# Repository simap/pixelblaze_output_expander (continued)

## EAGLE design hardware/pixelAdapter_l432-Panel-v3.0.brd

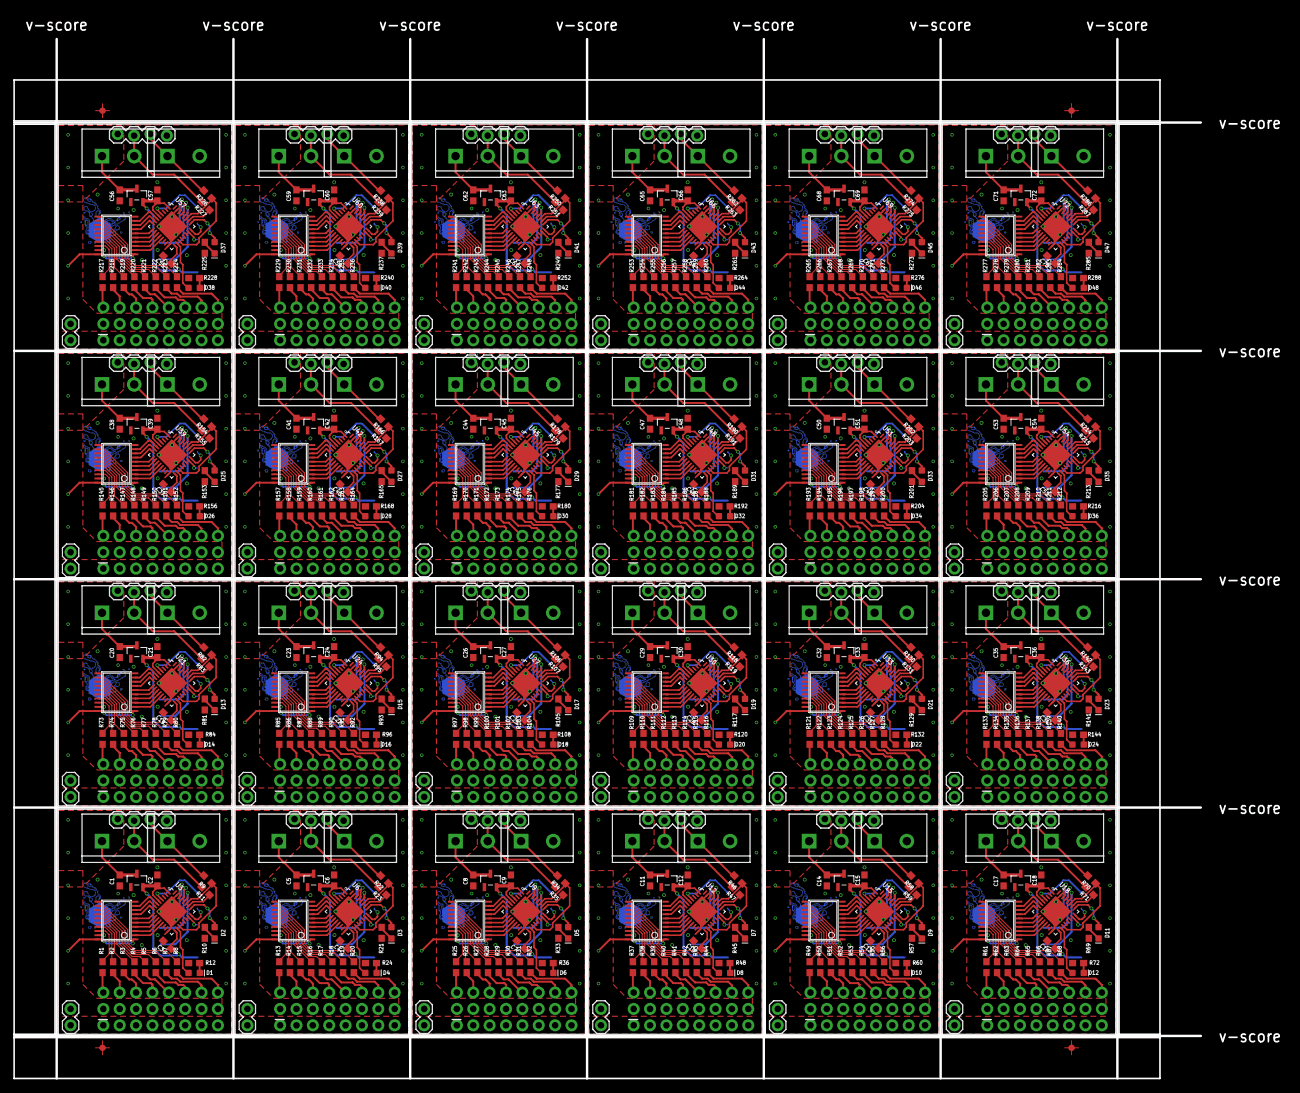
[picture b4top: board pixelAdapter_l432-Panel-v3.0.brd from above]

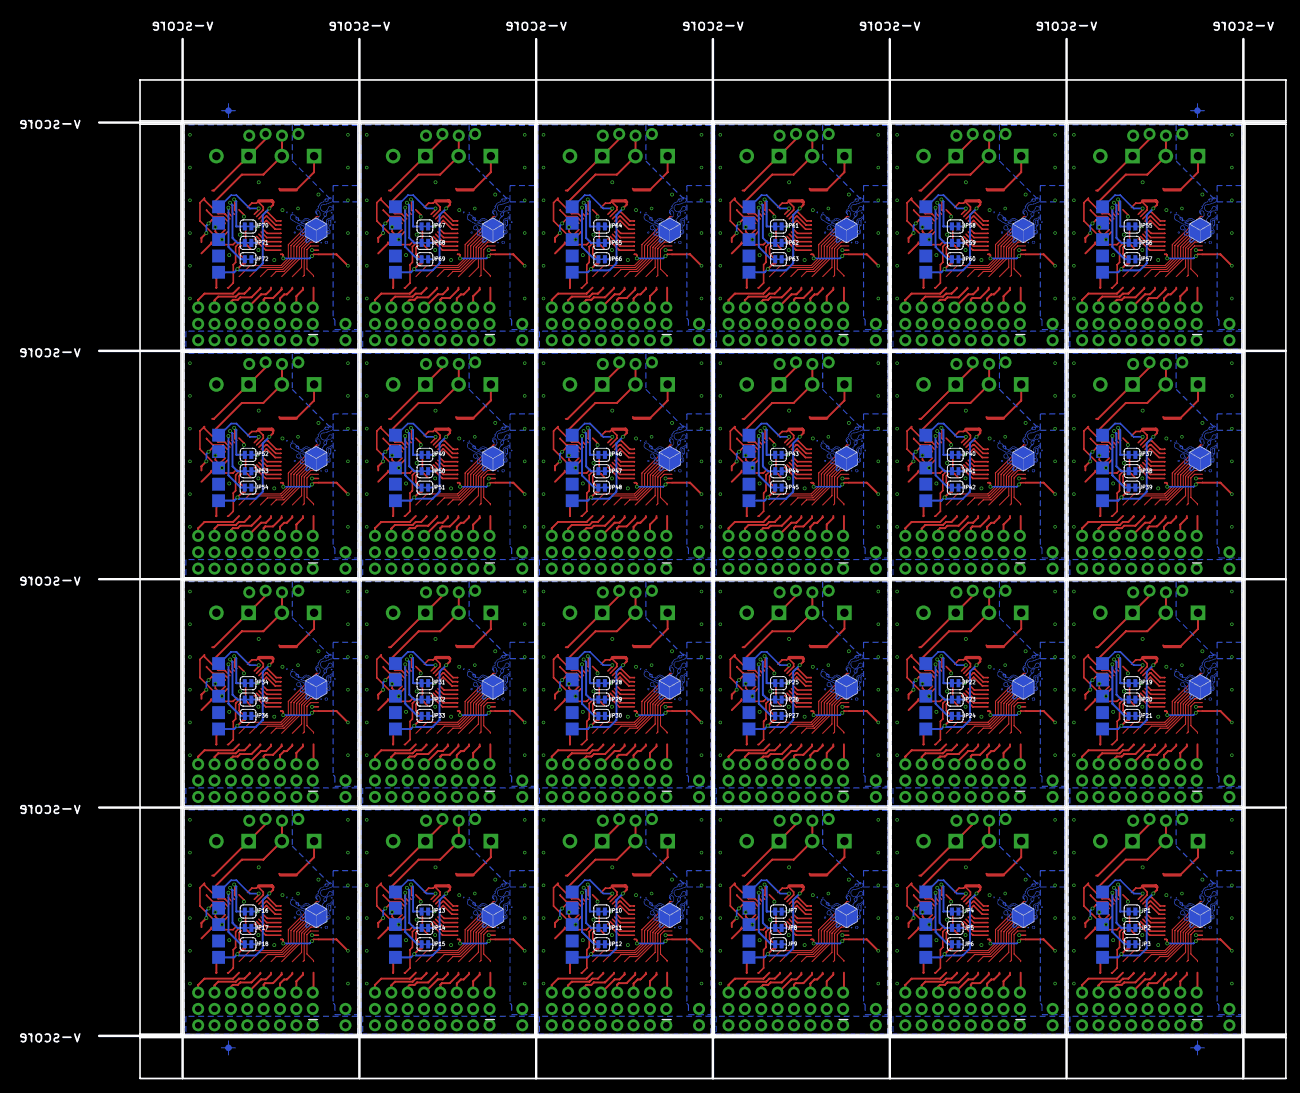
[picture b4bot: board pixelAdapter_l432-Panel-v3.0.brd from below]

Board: 2 copper layers, 184.2 x 161.3 mm, 848 parts (220 on the bottom side), 984 nets.

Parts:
C1, C2, C5, C6, C8, C9, C11, C12, C14, C15, C17, C18, C20, C21, C23, C24, C26, C27, C29, C30, C32, C33, C35, C36, C38, C39, C41, C42, C44, C45, C47, C48, C50, C51, C53, C54, C56, C57, C59, C60, C62, C63, C65, C66, C68, C69, C71, C72: 4.7uF; 0603
C3, C4, C7, C10, C13, C16, C19, C22, C25, C28, C31, C34, C37, C40, C43, C46, C49, C52, C55, C58, C61, C64, C67, C70: 0.1uF; 0603
D1, D4, D6, D8, D10, D12, D14, D16, D18, D20, D22, D24, D26, D28, D30, D32, D34, D36, D38, D40, D42, D44, D46, D48: GREEN; LED-0603
D2, D3, D5, D7, D9, D11, D13, D15, D17, D19, D21, D23, D25, D27, D29, D31, D33, D35, D37, D39, D41, D43, D45, D47: ORANGE; LED-0603
E$1, E$2, E$3, E$4, E$5, E$6, E$7, E$8: BENSFIDUCIAL-SMALL
J1, J11, J17, J23, J29, J35, J41, J47, J53, J59, J65, J71, J77, J83, J89, J95, J101, J107, J113, J119, J125, J131, J137, J143: 1X08_NO_SILK
J2, J7, J13, J19, J25, J31, J37, J43, J49, J55, J61, J67, J73, J79, J85, J91, J97, J103, J109, J115, J121, J127, J133, J139: 2X8-NOSILK
J3, J4, J8, J9, J14, J15, J20, J21, J26, J27, J32, J33, J38, J39, J44, J45, J50, J51, J56, J57, J62, J63, J68, J69, J74, J75, J80, J81, J86, J87, J92, J93, J98, J99, J104, J105, J110, J111, J116, J117, J122, J123, J128, J129, J134, J135, J140, J141: SCREWTERMINAL-5MM-2
J5, J10, J16, J22, J28, J34, J40, J46, J52, J58, J64, J70, J76, J82, J88, J94, J100, J106, J112, J118, J124, J130, J136, J142: 1X04_LOCK
J6, J12, J18, J24, J30, J36, J42, J48, J54, J60, J66, J72, J78, J84, J90, J96, J102, J108, J114, J120, J126, J132, J138, J144: 1X02
JP1, JP2, JP3, JP4, JP5, JP6, JP7, JP8, JP9, JP10, JP11, JP12, JP13, JP14, JP15, JP16, JP17, JP18, JP19, JP20, JP21, JP22, JP23, JP24, JP25, JP26, JP27, JP28, JP29, JP30, JP31, JP32, JP33, JP34, JP35, JP36, JP37, JP38, JP39, JP40, JP41, JP42, JP43, JP44, JP45, JP46, JP47, JP48, JP49, JP50, JP51, JP52, JP53, JP54, JP55, JP56, JP57, JP58, JP59, JP60, JP61, JP62, JP63, JP64, JP65, JP66, JP67, JP68, JP69, JP70, JP71, JP72: JUMPER-SMT_2_NC_TRACE_SILK; SMT-JUMPER_2_NC_TRACE_SILK
R1, R2, R3, R4, R5, R6, R7, R8, R9, R10, R11, R12, R13, R14, R15, R16, R17, R18, R19, R20, R21, R22, R23, R24, R25, R26, R27, R28, R29, R30, R31, R32, R33, R34, R35, R36, R37, R38, R39, R40, R41, R42, R43, R44, R45, R46, R47, R48, R49, R50, R51, R52, R53, R54, R55, R56, R57, R58, R59, R60, R61, R62, R63, R64, R65, R66, R67, R68, R69, R70, R71, R72, R73, R74, R75, R76, R77, R78, R79, R80, R81, R82, R83, R84, R85, R86, R87, R88, R89, R90, R91, R92, R93, R94, R95, R96, R97, R98, R99, R100, R101, R102, R103, R104, R105, R106, R107, R108, R109, R110, R111, R112, R113, R114, R115, R116, R117, R118, R119, R120, R121, R122, R123, R124, R125, R126, R127, R128, R129, R130, R131, R132, R133, R134, R135, R136, R137, R138, R139, R140, R141, R142, R143, R144, R145, R146, R147, R148, R149, R150, R151, R152, R153, R154, R155, R156, R157, R158, R159, R160, R161, R162, R163, R164, R165, R166, R167, R168, R169, R170, R171, R172, R173, R174, R175, R176, R177, R178, R179, R180, R181, R182, R183, R184, R185, R186, R187, R188, R189, R190, R191, R192, R193, R194, R195, R196, R197, R198, R199, R200, R201, R202, R203, R204, R205, R206, R207, R208, R209, R210, R211, R212, R213, R214, R215, R216, R217, R218, R219, R220, R221, R222, R223, R224, R225, R226, R227, R228, R229, R230, R231, R232, R233, R234, R235, R236, R237, R238, R239, R240, R241, R242, R243, R244, R245, R246, R247, R248, R249, R250, R251, R252, R253, R254, R255, R256, R257, R258, R259, R260, R261, R262, R263, R264, R265, R266, R267, R268, R269, R270, R271, R272, R273, R274, R275, R276, R277, R278, R279, R280, R281, R282, R283, R284, R285, R286, R287, R288: 100; 0603
TP1, TP2, TP3, TP4, TP5, TP6, TP7, TP8, TP9, TP10, TP11, TP12, TP13, TP14, TP15, TP16, TP17, TP18, TP19, TP20, TP21, TP22, TP23, TP24, TP25, TP26, TP27, TP28, TP29, TP30, TP31, TP32, TP33, TP34, TP35, TP36, TP37, TP38, TP39, TP40, TP41, TP42, TP43, TP44, TP45, TP46, TP47, TP48, TP49, TP50, TP51, TP52, TP53, TP54, TP55, TP56, TP57, TP58, TP59, TP60, TP61, TP62, TP63, TP64, TP65, TP66, TP67, TP68, TP69, TP70, TP71, TP72, TP73, TP74, TP75, TP76, TP77, TP78, TP79, TP80, TP81, TP82, TP83, TP84, TP85, TP86, TP87, TP88, TP89, TP90, TP91, TP92, TP93, TP94, TP95, TP96, TP97, TP98, TP99, TP100, TP101, TP102, TP103, TP104, TP105, TP106, TP107, TP108, TP109, TP110, TP111, TP112, TP113, TP114, TP115, TP116, TP117, TP118, TP119, TP120: TPTP20SQ; TP20SQ
U1, U4, U7, U10, U13, U16, U19, U22, U25, U28, U31, U34, U37, U40, U43, U46, U49, U52, U55, U58, U61, U64, U67, U70: SN74HCT245PWR; TSSOP20
U2, U5, U8, U11, U14, U17, U20, U23, U26, U29, U32, U35, U38, U41, U44, U47, U50, U53, U56, U59, U62, U65, U68, U71: AP2120N-3.3TRG1; SOT95P237X112-3N
U3, U6, U9, U12, U15, U18, U21, U24, U27, U30, U33, U36, U39, U42, U45, U48, U51, U54, U57, U60, U63, U66, U69, U72: STM32L432KCU6; QFN50P500X500X60-33N
U$1, U$2, U$3, U$4, U$5, U$6, U$7, U$8, U$9, U$10, U$11, U$12, U$13, U$14, U$15, U$16, U$17, U$18, U$19, U$20, U$21, U$22, U$23, U$24: ELECTRO_MAGE_PCB4_PIXEL_2#PNG

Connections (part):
5V: C1.1, J2.1, J2.3, J2.5, J2.7, J2.9, J2.11, J2.13, J2.15, J3.1, J5.4, J6.2, U1.1, U1.20, U2.3
5V1: C5.1, J7.1, J7.3, J7.5, J7.7, J7.9, J7.11, J7.13, J7.15, J8.1, J10.4, J12.2, U4.1, U4.20, U5.3
5V2: C8.1, J13.1, J13.3, J13.5, J13.7, J13.9, J13.11, J13.13, J13.15, J14.1, J16.4, J18.2, U7.1, U7.20, U8.3
5V3: C11.1, J19.1, J19.3, J19.5, J19.7, J19.9, J19.11, J19.13, J19.15, J20.1, J22.4, J24.2, U10.1, U10.20, U11.3
5V4: C14.1, J25.1, J25.3, J25.5, J25.7, J25.9, J25.11, J25.13, J25.15, J26.1, J28.4, J30.2, U13.1, U13.20, U14.3
5V5: C17.1, J31.1, J31.3, J31.5, J31.7, J31.9, J31.11, J31.13, J31.15, J32.1, J34.4, J36.2, U16.1, U16.20, U17.3
5V6: C20.1, J37.1, J37.3, J37.5, J37.7, J37.9, J37.11, J37.13, J37.15, J38.1, J40.4, J42.2, U19.1, U19.20, U20.3
5V7: C23.1, J43.1, J43.3, J43.5, J43.7, J43.9, J43.11, J43.13, J43.15, J44.1, J46.4, J48.2, U22.1, U22.20, U23.3
5V8: C26.1, J49.1, J49.3, J49.5, J49.7, J49.9, J49.11, J49.13, J49.15, J50.1, J52.4, J54.2, U25.1, U25.20, U26.3
5V9: C29.1, J55.1, J55.3, J55.5, J55.7, J55.9, J55.11, J55.13, J55.15, J56.1, J58.4, J60.2, U28.1, U28.20, U29.3
5V10: C32.1, J61.1, J61.3, J61.5, J61.7, J61.9, J61.11, J61.13, J61.15, J62.1, J64.4, J66.2, U31.1, U31.20, U32.3
5V11: C35.1, J67.1, J67.3, J67.5, J67.7, J67.9, J67.11, J67.13, J67.15, J68.1, J70.4, J72.2, U34.1, U34.20, U35.3
5V12: C38.1, J73.1, J73.3, J73.5, J73.7, J73.9, J73.11, J73.13, J73.15, J74.1, J76.4, J78.2, U37.1, U37.20, U38.3
5V13: C41.1, J79.1, J79.3, J79.5, J79.7, J79.9, J79.11, J79.13, J79.15, J80.1, J82.4, J84.2, U40.1, U40.20, U41.3
5V14: C44.1, J85.1, J85.3, J85.5, J85.7, J85.9, J85.11, J85.13, J85.15, J86.1, J88.4, J90.2, U43.1, U43.20, U44.3
5V15: C47.1, J91.1, J91.3, J91.5, J91.7, J91.9, J91.11, J91.13, J91.15, J92.1, J94.4, J96.2, U46.1, U46.20, U47.3
5V16: C50.1, J97.1, J97.3, J97.5, J97.7, J97.9, J97.11, J97.13, J97.15, J98.1, J100.4, J102.2, U49.1, U49.20, U50.3
5V17: C53.1, J103.1, J103.3, J103.5, J103.7, J103.9, J103.11, J103.13, J103.15, J104.1, J106.4, J108.2, U52.1, U52.20, U53.3
5V18: C56.1, J109.1, J109.3, J109.5, J109.7, J109.9, J109.11, J109.13, J109.15, J110.1, J112.4, J114.2, U55.1, U55.20, U56.3
5V19: C59.1, J115.1, J115.3, J115.5, J115.7, J115.9, J115.11, J115.13, J115.15, J116.1, J118.4, J120.2, U58.1, U58.20, U59.3
5V20: C62.1, J121.1, J121.3, J121.5, J121.7, J121.9, J121.11, J121.13, J121.15, J122.1, J124.4, J126.2, U61.1, U61.20, U62.3
5V21: C65.1, J127.1, J127.3, J127.5, J127.7, J127.9, J127.11, J127.13, J127.15, J128.1, J130.4, J132.2, U64.1, U64.20, U65.3
5V22: C68.1, J133.1, J133.3, J133.5, J133.7, J133.9, J133.11, J133.13, J133.15, J134.1, J136.4, J138.2, U67.1, U67.20, U68.3
5V23: C71.1, J139.1, J139.3, J139.5, J139.7, J139.9, J139.11, J139.13, J139.15, J140.1, J142.4, J144.2, U70.1, U70.20, U71.3
+3V1: C4.1, C6.1, TP9.TP, U5.2, U6.1, U6.5, U6.17
+3V2: C7.1, C9.1, TP14.TP, U8.2, U9.1, U9.5, U9.17
+3V3: C2.1, C3.1, TP4.TP, U2.2, U3.1, U3.5, U3.17
+3V4: C10.1, C12.1, TP19.TP, U11.2, U12.1, U12.5, U12.17
+3V5: C13.1, C15.1, TP24.TP, U14.2, U15.1, U15.5, U15.17
+3V6: C16.1, C18.1, TP29.TP, U17.2, U18.1, U18.5, U18.17
+3V7: C19.1, C21.1, TP34.TP, U20.2, U21.1, U21.5, U21.17
+3V8: C22.1, C24.1, TP39.TP, U23.2, U24.1, U24.5, U24.17
+3V9: C25.1, C27.1, TP44.TP, U26.2, U27.1, U27.5, U27.17
+3V10: C28.1, C30.1, TP49.TP, U29.2, U30.1, U30.5, U30.17
+3V11: C31.1, C33.1, TP54.TP, U32.2, U33.1, U33.5, U33.17
+3V12: C34.1, C36.1, TP59.TP, U35.2, U36.1, U36.5, U36.17
+3V13: C37.1, C39.1, TP64.TP, U38.2, U39.1, U39.5, U39.17
+3V14: C40.1, C42.1, TP69.TP, U41.2, U42.1, U42.5, U42.17
+3V15: C43.1, C45.1, TP74.TP, U44.2, U45.1, U45.5, U45.17
+3V16: C46.1, C48.1, TP79.TP, U47.2, U48.1, U48.5, U48.17
+3V17: C49.1, C51.1, TP84.TP, U50.2, U51.1, U51.5, U51.17
+3V18: C52.1, C54.1, TP89.TP, U53.2, U54.1, U54.5, U54.17
+3V19: C55.1, C57.1, TP94.TP, U56.2, U57.1, U57.5, U57.17
+3V20: C58.1, C60.1, TP99.TP, U59.2, U60.1, U60.5, U60.17
+3V21: C61.1, C63.1, TP104.TP, U62.2, U63.1, U63.5, U63.17
+3V22: C64.1, C66.1, TP109.TP, U65.2, U66.1, U66.5, U66.17
+3V23: C67.1, C69.1, TP114.TP, U68.2, U69.1, U69.5, U69.17
+3V24: C70.1, C72.1, TP119.TP, U71.2, U72.1, U72.5, U72.17
CH0: U1.2, U3.13
CH1: U1.3, U3.12
CH2: U1.4, U3.11
CH3: U1.5, U3.10
CH4: U1.6, U3.9
CH5: U1.7, U3.8
CH6: U1.8, U3.7
CH7: U1.9, U3.6
CH8: U4.9, U6.6
CH9: U4.8, U6.7
CH10: U4.7, U6.8
CH11: U4.2, U6.13
CH12: U4.3, U6.12
CH13: U4.4, U6.11
CH14: U4.5, U6.10
CH15: U4.6, U6.9
CH16: U7.9, U9.6
CH17: U7.8, U9.7
CH18: U7.7, U9.8
CH19: U7.2, U9.13
CH20: U7.3, U9.12
CH21: U7.4, U9.11
CH22: U7.5, U9.10
CH23: U7.6, U9.9
CH24: U10.9, U12.6
CH25: U10.8, U12.7
CH26: U10.7, U12.8
CH27: U10.2, U12.13
CH28: U10.3, U12.12
CH29: U10.4, U12.11
CH30: U10.5, U12.10
CH31: U10.6, U12.9
CH32: U13.9, U15.6
CH33: U13.8, U15.7
CH34: U13.7, U15.8
CH35: U13.2, U15.13
CH36: U13.3, U15.12
CH37: U13.4, U15.11
CH38: U13.5, U15.10
CH39: U13.6, U15.9
CH40: U16.9, U18.6
CH41: U16.8, U18.7
CH42: U16.7, U18.8
CH43: U16.2, U18.13
CH44: U16.3, U18.12
CH45: U16.4, U18.11
CH46: U16.5, U18.10
CH47: U16.6, U18.9
CH48: U19.9, U21.6
CH49: U19.8, U21.7
CH50: U19.7, U21.8
CH51: U19.2, U21.13
CH52: U19.3, U21.12
CH53: U19.4, U21.11
CH54: U19.5, U21.10
CH55: U19.6, U21.9
CH56: U22.9, U24.6
CH57: U22.8, U24.7
CH58: U22.7, U24.8
CH59: U22.2, U24.13
CH60: U22.3, U24.12
CH61: U22.4, U24.11
CH62: U22.5, U24.10
CH63: U22.6, U24.9
CH64: U25.9, U27.6
CH65: U25.8, U27.7
CH66: U25.7, U27.8
CH67: U25.2, U27.13
CH68: U25.3, U27.12
CH69: U25.4, U27.11
CH70: U25.5, U27.10
CH71: U25.6, U27.9
CH72: U28.9, U30.6
CH73: U28.8, U30.7
CH74: U28.7, U30.8
CH75: U28.2, U30.13
CH76: U28.3, U30.12
CH77: U28.4, U30.11
CH78: U28.5, U30.10
CH79: U28.6, U30.9
CH80: U31.9, U33.6
CH81: U31.8, U33.7
CH82: U31.7, U33.8
CH83: U31.2, U33.13
CH84: U31.3, U33.12
CH85: U31.4, U33.11
CH86: U31.5, U33.10
CH87: U31.6, U33.9
CH88: U34.9, U36.6
CH89: U34.8, U36.7
CH90: U34.7, U36.8
CH91: U34.2, U36.13
CH92: U34.3, U36.12
CH93: U34.4, U36.11
CH94: U34.5, U36.10
CH95: U34.6, U36.9
CH96: U37.9, U39.6
CH97: U37.8, U39.7
CH98: U37.7, U39.8
CH99: U37.2, U39.13
CH100: U37.3, U39.12
CH101: U37.4, U39.11
CH102: U37.5, U39.10
CH103: U37.6, U39.9
CH104: U40.9, U42.6
CH105: U40.8, U42.7
CH106: U40.7, U42.8
CH107: U40.2, U42.13
CH108: U40.3, U42.12
CH109: U40.4, U42.11
CH110: U40.5, U42.10
CH111: U40.6, U42.9
CH112: U43.9, U45.6
CH113: U43.8, U45.7
CH114: U43.7, U45.8
CH115: U43.2, U45.13
CH116: U43.3, U45.12
CH117: U43.4, U45.11
CH118: U43.5, U45.10
CH119: U43.6, U45.9
CH120: U46.9, U48.6
CH121: U46.8, U48.7
CH122: U46.7, U48.8
CH123: U46.2, U48.13
CH124: U46.3, U48.12
CH125: U46.4, U48.11
CH126: U46.5, U48.10
CH127: U46.6, U48.9
CH128: U49.9, U51.6
CH129: U49.8, U51.7
CH130: U49.7, U51.8
CH131: U49.2, U51.13
CH132: U49.3, U51.12
CH133: U49.4, U51.11
CH134: U49.5, U51.10
CH135: U49.6, U51.9
CH136: U52.9, U54.6
CH137: U52.8, U54.7
CH138: U52.7, U54.8
CH139: U52.2, U54.13
CH140: U52.3, U54.12
CH141: U52.4, U54.11
CH142: U52.5, U54.10
CH143: U52.6, U54.9
CH144: U55.9, U57.6
CH145: U55.8, U57.7
CH146: U55.7, U57.8
CH147: U55.2, U57.13
CH148: U55.3, U57.12
CH149: U55.4, U57.11
CH150: U55.5, U57.10
CH151: U55.6, U57.9
CH152: U58.9, U60.6
CH153: U58.8, U60.7
CH154: U58.7, U60.8
CH155: U58.2, U60.13
CH156: U58.3, U60.12
CH157: U58.4, U60.11
CH158: U58.5, U60.10
CH159: U58.6, U60.9
CH160: U61.9, U63.6
CH161: U61.8, U63.7
CH162: U61.7, U63.8
CH163: U61.2, U63.13
CH164: U61.3, U63.12
CH165: U61.4, U63.11
CH166: U61.5, U63.10
CH167: U61.6, U63.9
CH168: U64.9, U66.6
CH169: U64.8, U66.7
CH170: U64.7, U66.8
CH171: U64.2, U66.13
CH172: U64.3, U66.12
CH173: U64.4, U66.11
CH174: U64.5, U66.10
CH175: U64.6, U66.9
CH176: U67.9, U69.6
CH177: U67.8, U69.7
CH178: U67.7, U69.8
CH179: U67.2, U69.13
CH180: U67.3, U69.12
CH181: U67.4, U69.11
CH182: U67.5, U69.10
CH183: U67.6, U69.9
CH184: U70.9, U72.6
CH185: U70.8, U72.7
CH186: U70.7, U72.8
CH187: U70.2, U72.13
CH188: U70.3, U72.12
CH189: U70.4, U72.11
CH190: U70.5, U72.10
CH191: U70.6, U72.9
CLK: R11.1, U3.26
CLK1: R23.1, U6.26
CLK2: R35.1, U9.26
CLK3: R47.1, U12.26
CLK4: R59.1, U15.26
CLK5: R71.1, U18.26
CLK6: R83.1, U21.26
CLK7: R95.1, U24.26
CLK8: R107.1, U27.26
CLK9: R119.1, U30.26
CLK10: R131.1, U33.26
CLK11: R143.1, U36.26
CLK12: R155.1, U39.26
CLK13: R167.1, U42.26
CLK14: R179.1, U45.26
CLK15: R191.1, U48.26
CLK16: R203.1, U51.26
CLK17: R215.1, U54.26
CLK18: R227.1, U57.26
CLK19: R239.1, U60.26
CLK20: R251.1, U63.26
CLK21: R263.1, U66.26
CLK22: R275.1, U69.26
CLK23: R287.1, U72.26
CLK_IN: J3.2, J5.3, R11.2
CLK_IN1: J8.2, J10.3, R23.2
CLK_IN2: J14.2, J16.3, R35.2
CLK_IN3: J20.2, J22.3, R47.2
CLK_IN4: J26.2, J28.3, R59.2
CLK_IN5: J32.2, J34.3, R71.2
CLK_IN6: J38.2, J40.3, R83.2
CLK_IN7: J44.2, J46.3, R95.2
CLK_IN8: J50.2, J52.3, R107.2
CLK_IN9: J56.2, J58.3, R119.2
CLK_IN10: J62.2, J64.3, R131.2
CLK_IN11: J68.2, J70.3, R143.2
CLK_IN12: J74.2, J76.3, R155.2
CLK_IN13: J80.2, J82.3, R167.2
CLK_IN14: J86.2, J88.3, R179.2
CLK_IN15: J92.2, J94.3, R191.2
CLK_IN16: J98.2, J100.3, R203.2
CLK_IN17: J104.2, J106.3, R215.2
CLK_IN18: J110.2, J112.3, R227.2
CLK_IN19: J116.2, J118.3, R239.2
CLK_IN20: J122.2, J124.3, R251.2
CLK_IN21: J128.2, J130.3, R263.2
CLK_IN22: J134.2, J136.3, R275.2
CLK_IN23: J140.2, J142.3, R287.2
DAT_IN: J4.1, J5.2, R9.1
DAT_IN1: J9.1, J10.2, R22.1
DAT_IN2: J15.1, J16.2, R34.1
DAT_IN3: J21.1, J22.2, R46.1
DAT_IN4: J27.1, J28.2, R58.1
DAT_IN5: J33.1, J34.2, R70.1
DAT_IN6: J39.1, J40.2, R82.1
DAT_IN7: J45.1, J46.2, R94.1
DAT_IN8: J51.1, J52.2, R106.1
DAT_IN9: J57.1, J58.2, R118.1
DAT_IN10: J63.1, J64.2, R130.1
DAT_IN11: J69.1, J70.2, R142.1
DAT_IN12: J75.1, J76.2, R154.1
DAT_IN13: J81.1, J82.2, R166.1
DAT_IN14: J87.1, J88.2, R178.1
DAT_IN15: J93.1, J94.2, R190.1
DAT_IN16: J99.1, J100.2, R202.1
DAT_IN17: J105.1, J106.2, R214.1
DAT_IN18: J111.1, J112.2, R226.1
DAT_IN19: J117.1, J118.2, R238.1
DAT_IN20: J123.1, J124.2, R250.1
DAT_IN21: J129.1, J130.2, R262.1
DAT_IN22: J135.1, J136.2, R274.1
DAT_IN23: J141.1, J142.2, R286.1
GND: C1.2, C2.2, C3.2, J1.1, J1.2, J1.3, J1.4, J1.5, J1.6, J1.7, J1.8, J4.2, J5.1, J6.1, JP1.2, JP2.2, JP3.1, R10.2, R12.2, TP3.TP, U1.10, U1.19, U2.1, U3.16, U3.31, U3.32, U3.33
GND1: C4.2, C5.2, C6.2, J9.2, J10.1, J11.1, J11.2, J11.3, J11.4, J11.5, J11.6, J11.7, J11.8, J12.1, JP4.2, JP5.2, JP6.1, R21.2, R24.2, TP8.TP, U4.10, U4.19, U5.1, U6.16, U6.31, U6.32, U6.33
GND2: C7.2, C8.2, C9.2, J15.2, J16.1, J17.1, J17.2, J17.3, J17.4, J17.5, J17.6, J17.7, J17.8, J18.1, JP7.2, JP8.2, JP9.1, R33.2, R36.2, TP13.TP, U7.10, U7.19, U8.1, U9.16, U9.31, U9.32, U9.33
GND3: C10.2, C11.2, C12.2, J21.2, J22.1, J23.1, J23.2, J23.3, J23.4, J23.5, J23.6, J23.7, J23.8, J24.1, JP10.2, JP11.2, JP12.1, R45.2, R48.2, TP18.TP, U10.10, U10.19, U11.1, U12.16, U12.31, U12.32, U12.33
GND4: C13.2, C14.2, C15.2, J27.2, J28.1, J29.1, J29.2, J29.3, J29.4, J29.5, J29.6, J29.7, J29.8, J30.1, JP13.2, JP14.2, JP15.1, R57.2, R60.2, TP23.TP, U13.10, U13.19, U14.1, U15.16, U15.31, U15.32, U15.33
GND5: C16.2, C17.2, C18.2, J33.2, J34.1, J35.1, J35.2, J35.3, J35.4, J35.5, J35.6, J35.7, J35.8, J36.1, JP16.2, JP17.2, JP18.1, R69.2, R72.2, TP28.TP, U16.10, U16.19, U17.1, U18.16, U18.31, U18.32, U18.33
GND6: C19.2, C20.2, C21.2, J39.2, J40.1, J41.1, J41.2, J41.3, J41.4, J41.5, J41.6, J41.7, J41.8, J42.1, JP19.2, JP20.2, JP21.1, R81.2, R84.2, TP33.TP, U19.10, U19.19, U20.1, U21.16, U21.31, U21.32, U21.33
GND7: C22.2, C23.2, C24.2, J45.2, J46.1, J47.1, J47.2, J47.3, J47.4, J47.5, J47.6, J47.7, J47.8, J48.1, JP22.2, JP23.2, JP24.1, R93.2, R96.2, TP38.TP, U22.10, U22.19, U23.1, U24.16, U24.31, U24.32, U24.33
GND8: C25.2, C26.2, C27.2, J51.2, J52.1, J53.1, J53.2, J53.3, J53.4, J53.5, J53.6, J53.7, J53.8, J54.1, JP25.2, JP26.2, JP27.1, R105.2, R108.2, TP43.TP, U25.10, U25.19, U26.1, U27.16, U27.31, U27.32, U27.33
GND9: C28.2, C29.2, C30.2, J57.2, J58.1, J59.1, J59.2, J59.3, J59.4, J59.5, J59.6, J59.7, J59.8, J60.1, JP28.2, JP29.2, JP30.1, R117.2, R120.2, TP48.TP, U28.10, U28.19, U29.1, U30.16, U30.31, U30.32, U30.33
GND10: C31.2, C32.2, C33.2, J63.2, J64.1, J65.1, J65.2, J65.3, J65.4, J65.5, J65.6, J65.7, J65.8, J66.1, JP31.2, JP32.2, JP33.1, R129.2, R132.2, TP53.TP, U31.10, U31.19, U32.1, U33.16, U33.31, U33.32, U33.33
GND11: C34.2, C35.2, C36.2, J69.2, J70.1, J71.1, J71.2, J71.3, J71.4, J71.5, J71.6, J71.7, J71.8, J72.1, JP34.2, JP35.2, JP36.1, R141.2, R144.2, TP58.TP, U34.10, U34.19, U35.1, U36.16, U36.31, U36.32, U36.33
GND12: C37.2, C38.2, C39.2, J75.2, J76.1, J77.1, J77.2, J77.3, J77.4, J77.5, J77.6, J77.7, J77.8, J78.1, JP37.2, JP38.2, JP39.1, R153.2, R156.2, TP63.TP, U37.10, U37.19, U38.1, U39.16, U39.31, U39.32, U39.33
GND13: C40.2, C41.2, C42.2, J81.2, J82.1, J83.1, J83.2, J83.3, J83.4, J83.5, J83.6, J83.7, J83.8, J84.1, JP40.2, JP41.2, JP42.1, R165.2, R168.2, TP68.TP, U40.10, U40.19, U41.1, U42.16, U42.31, U42.32, U42.33
GND14: C43.2, C44.2, C45.2, J87.2, J88.1, J89.1, J89.2, J89.3, J89.4, J89.5, J89.6, J89.7, J89.8, J90.1, JP43.2, JP44.2, JP45.1, R177.2, R180.2, TP73.TP, U43.10, U43.19, U44.1, U45.16, U45.31, U45.32, U45.33
GND15: C46.2, C47.2, C48.2, J93.2, J94.1, J95.1, J95.2, J95.3, J95.4, J95.5, J95.6, J95.7, J95.8, J96.1, JP46.2, JP47.2, JP48.1, R189.2, R192.2, TP78.TP, U46.10, U46.19, U47.1, U48.16, U48.31, U48.32, U48.33
GND16: C49.2, C50.2, C51.2, J99.2, J100.1, J101.1, J101.2, J101.3, J101.4, J101.5, J101.6, J101.7, J101.8, J102.1, JP49.2, JP50.2, JP51.1, R201.2, R204.2, TP83.TP, U49.10, U49.19, U50.1, U51.16, U51.31, U51.32, U51.33
GND17: C52.2, C53.2, C54.2, J105.2, J106.1, J107.1, J107.2, J107.3, J107.4, J107.5, J107.6, J107.7, J107.8, J108.1, JP52.2, JP53.2, JP54.1, R213.2, R216.2, TP88.TP, U52.10, U52.19, U53.1, U54.16, U54.31, U54.32, U54.33
GND18: C55.2, C56.2, C57.2, J111.2, J112.1, J113.1, J113.2, J113.3, J113.4, J113.5, J113.6, J113.7, J113.8, J114.1, JP55.2, JP56.2, JP57.1, R225.2, R228.2, TP93.TP, U55.10, U55.19, U56.1, U57.16, U57.31, U57.32, U57.33
GND19: C58.2, C59.2, C60.2, J117.2, J118.1, J119.1, J119.2, J119.3, J119.4, J119.5, J119.6, J119.7, J119.8, J120.1, JP58.2, JP59.2, JP60.1, R237.2, R240.2, TP98.TP, U58.10, U58.19, U59.1, U60.16, U60.31, U60.32, U60.33
GND20: C61.2, C62.2, C63.2, J123.2, J124.1, J125.1, J125.2, J125.3, J125.4, J125.5, J125.6, J125.7, J125.8, J126.1, JP61.2, JP62.2, JP63.1, R249.2, R252.2, TP103.TP, U61.10, U61.19, U62.1, U63.16, U63.31, U63.32, U63.33
GND21: C64.2, C65.2, C66.2, J129.2, J130.1, J131.1, J131.2, J131.3, J131.4, J131.5, J131.6, J131.7, J131.8, J132.1, JP64.2, JP65.2, JP66.1, R261.2, R264.2, TP108.TP, U64.10, U64.19, U65.1, U66.16, U66.31, U66.32, U66.33
GND22: C67.2, C68.2, C69.2, J135.2, J136.1, J137.1, J137.2, J137.3, J137.4, J137.5, J137.6, J137.7, J137.8, J138.1, JP67.2, JP68.2, JP69.1, R273.2, R276.2, TP113.TP, U67.10, U67.19, U68.1, U69.16, U69.31, U69.32, U69.33
GND23: C70.2, C71.2, C72.2, J141.2, J142.1, J143.1, J143.2, J143.3, J143.4, J143.5, J143.6, J143.7, J143.8, J144.1, JP70.2, JP71.2, JP72.1, R285.2, R288.2, TP118.TP, U70.10, U70.19, U71.1, U72.16, U72.31, U72.32, U72.33
JP1: JP1.1, U3.30
JP2: JP2.1, U3.29
JP3: JP3.2, U3.28
JP4: JP4.1, U6.30
JP5: JP5.1, U6.29
JP6: JP6.2, U6.28
JP7: JP7.1, U9.30
JP8: JP8.1, U9.29
JP9: JP9.2, U9.28
JP10: JP10.1, U12.30
JP11: JP11.1, U12.29
JP12: JP12.2, U12.28
JP13: JP13.1, U15.30
JP14: JP14.1, U15.29
JP15: JP15.2, U15.28
JP16: JP16.1, U18.30
JP17: JP17.1, U18.29
JP18: JP18.2, U18.28
JP19: JP19.1, U21.30
JP20: JP20.1, U21.29
JP21: JP21.2, U21.28
JP22: JP22.1, U24.30
JP23: JP23.1, U24.29
JP24: JP24.2, U24.28
JP25: JP25.1, U27.30
JP26: JP26.1, U27.29
JP27: JP27.2, U27.28
JP28: JP28.1, U30.30
JP29: JP29.1, U30.29
JP30: JP30.2, U30.28
JP31: JP31.1, U33.30
JP32: JP32.1, U33.29
JP33: JP33.2, U33.28
JP34: JP34.1, U36.30
JP35: JP35.1, U36.29
JP36: JP36.2, U36.28
JP37: JP37.1, U39.30
JP38: JP38.1, U39.29
JP39: JP39.2, U39.28
JP40: JP40.1, U42.30
JP41: JP41.1, U42.29
JP42: JP42.2, U42.28
JP43: JP43.1, U45.30
JP44: JP44.1, U45.29
JP45: JP45.2, U45.28
JP46: JP46.1, U48.30
JP47: JP47.1, U48.29
JP48: JP48.2, U48.28
JP49: JP49.1, U51.30
JP50: JP50.1, U51.29
JP51: JP51.2, U51.28
JP52: JP52.1, U54.30
JP53: JP53.1, U54.29
JP54: JP54.2, U54.28
JP55: JP55.1, U57.30
JP56: JP56.1, U57.29
JP57: JP57.2, U57.28
JP58: JP58.1, U60.30
JP59: JP59.1, U60.29
JP60: JP60.2, U60.28
JP61: JP61.1, U63.30
JP62: JP62.1, U63.29
JP63: JP63.2, U63.28
JP64: JP64.1, U66.30
JP65: JP65.1, U66.29
JP66: JP66.2, U66.28
JP67: JP67.1, U69.30
JP68: JP68.1, U69.29
JP69: JP69.2, U69.28
JP70: JP70.1, U72.30
JP71: JP71.1, U72.29
JP72: JP72.2, U72.28
LED0: J2.2, R1.2
LED1: J2.4, R2.2
LED2: J2.6, R3.2
LED3: J2.8, R4.2
LED4: J2.10, R5.2
LED5: J2.12, R6.2
LED6: J2.14, R7.2
LED7: J2.16, R8.2
LED8: J7.12, R18.2
LED9: J7.10, R17.2
LED10: J7.8, R16.2
LED11: J7.6, R15.2
LED12: J7.4, R14.2
LED13: J7.2, R13.2
LED14: J7.14, R19.2
LED15: J7.16, R20.2
LED16: J13.12, R30.2
LED17: J13.10, R29.2
LED18: J13.8, R28.2
LED19: J13.6, R27.2
LED20: J13.4, R26.2
LED21: J13.2, R25.2
LED22: J13.14, R31.2
LED23: J13.16, R32.2
LED24: J19.12, R42.2
LED25: J19.10, R41.2
LED26: J19.8, R40.2
LED27: J19.6, R39.2
LED28: J19.4, R38.2
LED29: J19.2, R37.2
LED30: J19.14, R43.2
LED31: J19.16, R44.2
LED32: J25.12, R54.2
LED33: J25.10, R53.2
LED34: J25.8, R52.2
LED35: J25.6, R51.2
LED36: J25.4, R50.2
LED37: J25.2, R49.2
LED38: J25.14, R55.2
LED39: J25.16, R56.2
LED40: J31.12, R66.2
LED41: J31.10, R65.2
LED42: J31.8, R64.2
LED43: J31.6, R63.2
LED44: J31.4, R62.2
LED45: J31.2, R61.2
LED46: J31.14, R67.2
LED47: J31.16, R68.2
LED48: J37.12, R78.2
LED49: J37.10, R77.2
LED50: J37.8, R76.2
LED51: J37.6, R75.2
LED52: J37.4, R74.2
LED53: J37.2, R73.2
LED54: J37.14, R79.2
LED55: J37.16, R80.2
LED56: J43.12, R90.2
LED57: J43.10, R89.2
LED58: J43.8, R88.2
LED59: J43.6, R87.2
LED60: J43.4, R86.2
LED61: J43.2, R85.2
LED62: J43.14, R91.2
LED63: J43.16, R92.2
LED64: J49.12, R102.2
LED65: J49.10, R101.2
LED66: J49.8, R100.2
LED67: J49.6, R99.2
LED68: J49.4, R98.2
LED69: J49.2, R97.2
LED70: J49.14, R103.2
LED71: J49.16, R104.2
LED72: J55.12, R114.2
LED73: J55.10, R113.2
LED74: J55.8, R112.2
LED75: J55.6, R111.2
LED76: J55.4, R110.2
LED77: J55.2, R109.2
LED78: J55.14, R115.2
LED79: J55.16, R116.2
LED80: J61.12, R126.2
LED81: J61.10, R125.2
LED82: J61.8, R124.2
LED83: J61.6, R123.2
LED84: J61.4, R122.2
LED85: J61.2, R121.2
LED86: J61.14, R127.2
LED87: J61.16, R128.2
LED88: J67.12, R138.2
LED89: J67.10, R137.2
LED90: J67.8, R136.2
LED91: J67.6, R135.2
LED92: J67.4, R134.2
LED93: J67.2, R133.2
LED94: J67.14, R139.2
LED95: J67.16, R140.2
LED96: J73.12, R150.2
LED97: J73.10, R149.2
LED98: J73.8, R148.2
LED99: J73.6, R147.2
LED100: J73.4, R146.2
LED101: J73.2, R145.2
LED102: J73.14, R151.2
LED103: J73.16, R152.2
LED104: J79.12, R162.2
LED105: J79.10, R161.2
LED106: J79.8, R160.2
LED107: J79.6, R159.2
LED108: J79.4, R158.2
LED109: J79.2, R157.2
LED110: J79.14, R163.2
LED111: J79.16, R164.2
LED112: J85.12, R174.2
LED113: J85.10, R173.2
LED114: J85.8, R172.2
LED115: J85.6, R171.2
LED116: J85.4, R170.2
LED117: J85.2, R169.2
LED118: J85.14, R175.2
LED119: J85.16, R176.2
LED120: J91.12, R186.2
LED121: J91.10, R185.2
LED122: J91.8, R184.2
LED123: J91.6, R183.2
LED124: J91.4, R182.2
LED125: J91.2, R181.2
LED126: J91.14, R187.2
LED127: J91.16, R188.2
LED128: J97.12, R198.2
LED129: J97.10, R197.2
LED130: J97.8, R196.2
LED131: J97.6, R195.2
LED132: J97.4, R194.2
LED133: J97.2, R193.2
LED134: J97.14, R199.2
LED135: J97.16, R200.2
LED136: J103.12, R210.2
LED137: J103.10, R209.2
LED138: J103.8, R208.2
LED139: J103.6, R207.2
LED140: J103.4, R206.2
LED141: J103.2, R205.2
LED142: J103.14, R211.2
LED143: J103.16, R212.2
LED144: J109.12, R222.2
LED145: J109.10, R221.2
LED146: J109.8, R220.2
LED147: J109.6, R219.2
LED148: J109.4, R218.2
LED149: J109.2, R217.2
LED150: J109.14, R223.2
LED151: J109.16, R224.2
LED152: J115.12, R234.2
LED153: J115.10, R233.2
LED154: J115.8, R232.2
LED155: J115.6, R231.2
LED156: J115.4, R230.2
LED157: J115.2, R229.2
LED158: J115.14, R235.2
LED159: J115.16, R236.2
LED160: J121.12, R246.2
LED161: J121.10, R245.2
LED162: J121.8, R244.2
LED163: J121.6, R243.2
LED164: J121.4, R242.2
LED165: J121.2, R241.2
LED166: J121.14, R247.2
LED167: J121.16, R248.2
LED168: J127.12, R258.2
LED169: J127.10, R257.2
LED170: J127.8, R256.2
LED171: J127.6, R255.2
LED172: J127.4, R254.2
LED173: J127.2, R253.2
LED174: J127.14, R259.2
LED175: J127.16, R260.2
LED176: J133.12, R270.2
LED177: J133.10, R269.2
LED178: J133.8, R268.2
LED179: J133.6, R267.2
LED180: J133.4, R266.2
LED181: J133.2, R265.2
LED182: J133.14, R271.2
LED183: J133.16, R272.2
LED184: J139.12, R282.2
LED185: J139.10, R281.2
LED186: J139.8, R280.2
LED187: J139.6, R279.2
LED188: J139.4, R278.2
LED189: J139.2, R277.2
LED190: J139.14, R283.2
LED191: J139.16, R284.2
LED_G: D1.A, U3.18
LED_G1: D4.A, U6.18
LED_G2: D6.A, U9.18
LED_G3: D8.A, U12.18
LED_G4: D10.A, U15.18
LED_G5: D12.A, U18.18
LED_G6: D14.A, U21.18
LED_G7: D16.A, U24.18
LED_G8: D18.A, U27.18
LED_G9: D20.A, U30.18
LED_G10: D22.A, U33.18
LED_G11: D24.A, U36.18
LED_G12: D26.A, U39.18
LED_G13: D28.A, U42.18
LED_G14: D30.A, U45.18
LED_G15: D32.A, U48.18
LED_G16: D34.A, U51.18
LED_G17: D36.A, U54.18
LED_G18: D38.A, U57.18
LED_G19: D40.A, U60.18
LED_G20: D42.A, U63.18
LED_G21: D44.A, U66.18
LED_G22: D46.A, U69.18
LED_G23: D48.A, U72.18
LED_O: D2.A, U3.25
LED_O1: D3.A, U6.25
LED_O2: D5.A, U9.25
LED_O3: D7.A, U12.25
LED_O4: D9.A, U15.25
LED_O5: D11.A, U18.25
LED_O6: D13.A, U21.25
LED_O7: D15.A, U24.25
LED_O8: D17.A, U27.25
LED_O9: D19.A, U30.25
LED_O10: D21.A, U33.25
LED_O11: D23.A, U36.25
LED_O12: D25.A, U39.25
LED_O13: D27.A, U42.25
LED_O14: D29.A, U45.25
LED_O15: D31.A, U48.25
LED_O16: D33.A, U51.25
LED_O17: D35.A, U54.25
LED_O18: D37.A, U57.25
LED_O19: D39.A, U60.25
LED_O20: D41.A, U63.25
LED_O21: D43.A, U66.25
LED_O22: D45.A, U69.25
LED_O23: D47.A, U72.25
unnamed: R13.1, U4.18
unnamed: D1.C, R12.1
unnamed: R14.1, U4.17
unnamed: R15.1, U4.16
unnamed: R16.1, U4.15
unnamed: R17.1, U4.14
unnamed: R18.1, U4.13
unnamed: R19.1, U4.12
unnamed: R20.1, U4.11
unnamed: D3.C, R21.1
unnamed: D4.C, R24.1
unnamed: R1.1, U1.18
unnamed: R2.1, U1.17
unnamed: R3.1, U1.16
unnamed: R4.1, U1.15
unnamed: R5.1, U1.14
unnamed: R6.1, U1.13
unnamed: R7.1, U1.12
unnamed: R8.1, U1.11
unnamed: R25.1, U7.18
unnamed: D2.C, R10.1
unnamed: R26.1, U7.17
unnamed: R27.1, U7.16
unnamed: R28.1, U7.15
unnamed: R29.1, U7.14
unnamed: R30.1, U7.13
unnamed: R31.1, U7.12
unnamed: R32.1, U7.11
unnamed: D5.C, R33.1
unnamed: D6.C, R36.1
unnamed: R37.1, U10.18
unnamed: R38.1, U10.17
unnamed: R39.1, U10.16
unnamed: R40.1, U10.15
unnamed: R41.1, U10.14
unnamed: R42.1, U10.13
unnamed: R43.1, U10.12
unnamed: R44.1, U10.11
unnamed: D7.C, R45.1
unnamed: D8.C, R48.1
unnamed: R49.1, U13.18
unnamed: R50.1, U13.17
unnamed: R51.1, U13.16
unnamed: R52.1, U13.15
unnamed: R53.1, U13.14
unnamed: R54.1, U13.13
unnamed: R55.1, U13.12
unnamed: R56.1, U13.11
unnamed: D9.C, R57.1
unnamed: D10.C, R60.1
unnamed: R61.1, U16.18
unnamed: R62.1, U16.17
unnamed: R63.1, U16.16
unnamed: R64.1, U16.15
unnamed: R65.1, U16.14
unnamed: R66.1, U16.13
unnamed: R67.1, U16.12
unnamed: R68.1, U16.11
unnamed: D11.C, R69.1
unnamed: D12.C, R72.1
unnamed: R73.1, U19.18
unnamed: R74.1, U19.17
unnamed: R75.1, U19.16
unnamed: R76.1, U19.15
unnamed: R77.1, U19.14
unnamed: R78.1, U19.13
unnamed: R79.1, U19.12
unnamed: R80.1, U19.11
unnamed: D13.C, R81.1
unnamed: D14.C, R84.1
unnamed: R85.1, U22.18
unnamed: R86.1, U22.17
unnamed: R87.1, U22.16
unnamed: R88.1, U22.15
unnamed: R89.1, U22.14
unnamed: R90.1, U22.13
unnamed: R91.1, U22.12
unnamed: R92.1, U22.11
unnamed: D15.C, R93.1
unnamed: D16.C, R96.1
unnamed: R97.1, U25.18
unnamed: R98.1, U25.17
unnamed: R99.1, U25.16
unnamed: R100.1, U25.15
unnamed: R101.1, U25.14
unnamed: R102.1, U25.13
unnamed: R103.1, U25.12
unnamed: R104.1, U25.11
unnamed: D17.C, R105.1
unnamed: D18.C, R108.1
unnamed: R109.1, U28.18
unnamed: R110.1, U28.17
unnamed: R111.1, U28.16
unnamed: R112.1, U28.15
unnamed: R113.1, U28.14
unnamed: R114.1, U28.13
unnamed: R115.1, U28.12
unnamed: R116.1, U28.11
unnamed: D19.C, R117.1
unnamed: D20.C, R120.1
unnamed: R121.1, U31.18
unnamed: R122.1, U31.17
unnamed: R123.1, U31.16
unnamed: R124.1, U31.15
unnamed: R125.1, U31.14
unnamed: R126.1, U31.13
unnamed: R127.1, U31.12
unnamed: R128.1, U31.11
unnamed: D21.C, R129.1
unnamed: D22.C, R132.1
unnamed: R133.1, U34.18
unnamed: R134.1, U34.17
unnamed: R135.1, U34.16
unnamed: R136.1, U34.15
unnamed: R137.1, U34.14
unnamed: R138.1, U34.13
unnamed: R139.1, U34.12
unnamed: R140.1, U34.11
unnamed: D23.C, R141.1
unnamed: D24.C, R144.1
unnamed: R145.1, U37.18
unnamed: R146.1, U37.17
unnamed: R147.1, U37.16
unnamed: R148.1, U37.15
unnamed: R149.1, U37.14
unnamed: R150.1, U37.13
unnamed: R151.1, U37.12
unnamed: R152.1, U37.11
unnamed: D25.C, R153.1
unnamed: D26.C, R156.1
unnamed: R157.1, U40.18
unnamed: R158.1, U40.17
unnamed: R159.1, U40.16
unnamed: R160.1, U40.15
unnamed: R161.1, U40.14
unnamed: R162.1, U40.13
unnamed: R163.1, U40.12
unnamed: R164.1, U40.11
unnamed: D27.C, R165.1
unnamed: D28.C, R168.1
unnamed: R169.1, U43.18
unnamed: R170.1, U43.17
unnamed: R171.1, U43.16
unnamed: R172.1, U43.15
unnamed: R173.1, U43.14
unnamed: R174.1, U43.13
unnamed: R175.1, U43.12
unnamed: R176.1, U43.11
unnamed: D29.C, R177.1
unnamed: D30.C, R180.1
unnamed: R181.1, U46.18
unnamed: R182.1, U46.17
unnamed: R183.1, U46.16
unnamed: R184.1, U46.15
unnamed: R185.1, U46.14
unnamed: R186.1, U46.13
unnamed: R187.1, U46.12
unnamed: R188.1, U46.11
unnamed: D31.C, R189.1
unnamed: D32.C, R192.1
unnamed: R193.1, U49.18
unnamed: R194.1, U49.17
unnamed: R195.1, U49.16
unnamed: R196.1, U49.15
unnamed: R197.1, U49.14
unnamed: R198.1, U49.13
unnamed: R199.1, U49.12
unnamed: R200.1, U49.11
unnamed: D33.C, R201.1
unnamed: D34.C, R204.1
unnamed: R205.1, U52.18
unnamed: R206.1, U52.17
unnamed: R207.1, U52.16
unnamed: R208.1, U52.15
unnamed: R209.1, U52.14
unnamed: R210.1, U52.13
unnamed: R211.1, U52.12
unnamed: R212.1, U52.11
unnamed: D35.C, R213.1
unnamed: D36.C, R216.1
unnamed: R217.1, U55.18
unnamed: R218.1, U55.17
unnamed: R219.1, U55.16
unnamed: R220.1, U55.15
unnamed: R221.1, U55.14
unnamed: R222.1, U55.13
unnamed: R223.1, U55.12
unnamed: R224.1, U55.11
unnamed: D37.C, R225.1
unnamed: D38.C, R228.1
unnamed: R229.1, U58.18
unnamed: R230.1, U58.17
unnamed: R231.1, U58.16
unnamed: R232.1, U58.15
unnamed: R233.1, U58.14
unnamed: R234.1, U58.13
unnamed: R235.1, U58.12
unnamed: R236.1, U58.11
unnamed: D39.C, R237.1
unnamed: D40.C, R240.1
unnamed: R241.1, U61.18
unnamed: R242.1, U61.17
unnamed: R243.1, U61.16
unnamed: R244.1, U61.15
unnamed: R245.1, U61.14
unnamed: R246.1, U61.13
unnamed: R247.1, U61.12
unnamed: R248.1, U61.11
unnamed: D41.C, R249.1
unnamed: D42.C, R252.1
unnamed: R253.1, U64.18
unnamed: R254.1, U64.17
unnamed: R255.1, U64.16
unnamed: R256.1, U64.15
unnamed: R257.1, U64.14
unnamed: R258.1, U64.13
unnamed: R259.1, U64.12
unnamed: R260.1, U64.11
unnamed: D43.C, R261.1
unnamed: D44.C, R264.1
unnamed: R265.1, U67.18
unnamed: R266.1, U67.17
unnamed: R267.1, U67.16
unnamed: R268.1, U67.15
unnamed: R269.1, U67.14
unnamed: R270.1, U67.13
unnamed: R271.1, U67.12
unnamed: R272.1, U67.11
unnamed: D45.C, R273.1
unnamed: D46.C, R276.1
unnamed: R277.1, U70.18
unnamed: R278.1, U70.17
unnamed: R279.1, U70.16
unnamed: R280.1, U70.15
unnamed: R281.1, U70.14
unnamed: R282.1, U70.13
unnamed: R283.1, U70.12
unnamed: R284.1, U70.11
unnamed: D47.C, R285.1
unnamed: D48.C, R288.1
NRST: TP5.TP, U3.4
NRST1: TP10.TP, U6.4
NRST2: TP15.TP, U9.4
NRST3: TP20.TP, U12.4
NRST4: TP25.TP, U15.4
NRST5: TP30.TP, U18.4
NRST6: TP35.TP, U21.4
NRST7: TP40.TP, U24.4
NRST8: TP45.TP, U27.4
NRST9: TP50.TP, U30.4
NRST10: TP55.TP, U33.4
NRST11: TP60.TP, U36.4
NRST12: TP65.TP, U39.4
NRST13: TP70.TP, U42.4
NRST14: TP75.TP, U45.4
NRST15: TP80.TP, U48.4
NRST16: TP85.TP, U51.4
NRST17: TP90.TP, U54.4
NRST18: TP95.TP, U57.4
NRST19: TP100.TP, U60.4
NRST20: TP105.TP, U63.4
NRST21: TP110.TP, U66.4
NRST22: TP115.TP, U69.4
NRST23: TP120.TP, U72.4
RX: R9.2, U3.19, U3.27
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
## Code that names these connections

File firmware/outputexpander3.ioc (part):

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Mcu.Name=STM32L432K(B-C)Ux
Mcu.Package=UFQFPN32
Mcu.UserName=STM32L432KBUx
PA0.GPIOParameters=GPIO_Speed
PA0.GPIO_Speed=GPIO_SPEED_FREQ_HIGH
PA0.Signal=GPIO_Output
PA1.GPIOParameters=GPIO_Speed
PA1.GPIO_Speed=GPIO_SPEED_FREQ_HIGH
PA1.Signal=GPIO_Output
PA13\ (JTMS-SWDIO).Mode=Serial_Wire
PA13\ (JTMS-SWDIO).Signal=SYS_JTMS-SWDIO
PA14\ (JTCK-SWCLK).Mode=Serial_Wire
PA14\ (JTCK-SWCLK).Signal=SYS_JTCK-SWCLK
PA15\ (JTDI).GPIOParameters=GPIO_Speed
PA15\ (JTDI).GPIO_Speed=GPIO_SPEED_FREQ_MEDIUM
PA15\ (JTDI).Signal=S_TIM2_CH1
PA2.GPIOParameters=GPIO_Speed
PA2.GPIO_Speed=GPIO_SPEED_FREQ_HIGH
PA2.Signal=GPIO_Output
PA3.GPIOParameters=GPIO_Speed
PA3.GPIO_Speed=GPIO_SPEED_FREQ_HIGH
PA3.Signal=GPIO_Output
PA4.GPIOParameters=GPIO_Speed
PA4.GPIO_Speed=GPIO_SPEED_FREQ_HIGH
PA4.Signal=GPIO_Output
PA5.GPIOParameters=GPIO_Speed
PA5.GPIO_Speed=GPIO_SPEED_FREQ_HIGH
PA5.Signal=GPIO_Output
PA6.GPIOParameters=GPIO_Speed
PA6.GPIO_Speed=GPIO_SPEED_FREQ_HIGH
PA6.Signal=GPIO_Output
PA7.GPIOParameters=GPIO_Speed
PA7.GPIO_Speed=GPIO_SPEED_FREQ_HIGH
PA7.Signal=GPIO_Output
PA8.GPIOParameters=GPIO_Speed
PA8.GPIO_Speed=GPIO_SPEED_FREQ_MEDIUM
PA8.Mode=WaveformGeneration
PA8.Signal=LPTIM2_OUT
PA9.Mode=Half_duplex(single_wire_mode)
PA9.Signal=USART1_TX
PB3\ (JTDO-TRACESWO).Mode=Simplex_Bidirectional_Slave
PB3\ (JTDO-TRACESWO).Signal=SPI1_SCK
PB4\ (NJTRST).Mode=Simplex_Bidirectional_Slave
PB4\ (NJTRST).Signal=SPI1_MISO
PB5.GPIOParameters=GPIO_PuPd
PB5.GPIO_PuPd=GPIO_PULLUP
PB5.Signal=GPIO_Input
PB6.GPIOParameters=GPIO_PuPd
PB6.GPIO_PuPd=GPIO_PULLUP
PB6.Signal=GPIO_Input
PB7.GPIOParameters=GPIO_PuPd
PB7.GPIO_PuPd=GPIO_PULLUP
PB7.Signal=GPIO_Input
RCC.HSE_VALUE=8000000
RCC.SYSCLKFreq_VALUE=80000000
RCC.SYSCLKSource=RCC_SYSCLKSOURCE_PLLCLK
board=custom

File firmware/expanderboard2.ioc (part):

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Mcu.Name=STM32F103C(8-B)Tx
Mcu.Package=LQFP48
Mcu.UserName=STM32F103C8Tx
PA0-WKUP.Signal=GPIO_Output
PA1.Signal=GPIO_Output
PA13.Mode=Serial_Wire
PA13.Signal=SYS_JTMS-SWDIO
PA14.Mode=Serial_Wire
PA14.Signal=SYS_JTCK-SWCLK
PA2.Signal=GPIO_Output
PA3.Signal=GPIO_Output
PA4.Signal=GPIO_Output
PA5.Signal=GPIO_Output
PA6.Signal=GPIO_Output
PA7.Signal=GPIO_Output
PA9.Mode=Half_duplex(single_wire_mode)
PA9.Signal=USART1_TX
PB0.GPIOParameters=GPIO_PuPd
PB0.GPIO_PuPd=GPIO_PULLUP
PB0.Signal=GPIO_Input
PB1.GPIOParameters=GPIO_PuPd
PB1.GPIO_PuPd=GPIO_PULLUP
PB1.Signal=GPIO_Input
PB2.GPIOParameters=GPIO_PuPd
PB2.GPIO_PuPd=GPIO_PULLUP
PB2.Signal=GPIO_Input
PC15-OSC32_OUT.Signal=GPIO_Output
RCC.SYSCLKFreq_VALUE=64000000
RCC.SYSCLKSource=RCC_SYSCLKSOURCE_PLLCLK
board=custom

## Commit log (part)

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2018-11-15 initial, working ish
    need to swap tim1 and tim2, but its working
    dma driving ws2812 via timers and tricks
2018-11-25 working, adding timeout and reset autobaud
2018-11-25 last attempt to make auto baud rate work
2018-11-27 WIP trying to debug stack corruption, moving chipsets, add tim14 for us
2018-11-27 WIP switch chipsets, need to move tim2 to tim3
2018-11-29 working, but still a few small dma glitches
2018-11-29 fix dma glitch
2018-12-16 fix bitconverter, dma glitch
2018-12-16 cleanup
2018-12-16 readme
2018-12-16 typo
2018-12-16 more cleanup
2018-12-17 swap channel order to match hw
2019-02-07 hardware files
2019-02-07 schematic pdf
2019-12-19 stm32f103 variant
2019-12-19 port to stm32f103 and use new cube ide
    also rename directory to firmware
2019-12-19 find the max bytes any channel wants to send and calculate TIM3 time
2020-02-17 working w/ both 2812 and apa102
2020-03-02 dma latency issues, add some nops, lessen interrupts. WIP
2020-03-02 update ioc
2020-03-02 remove all timer interrupts, use a one shot for ws2812 latch
    also for some reason, nops in bit converter code dont
2020-03-02 binaries
2020-06-14 Replaced wrong "UPLX" magic string in comment with "UPXL"
2020-07-31 pro boards v1.1
2020-07-31 remove some unused symbols
2020-07-31 remove unused symbols
2020-08-01 clean up schematics a little, get pdfs
2021-02-17 v3.0 boards
2021-02-18 port to stm32l432
    mostly switching timers/dma channels around and adjust timings
    added another status LED, both via PWM
    boost memory in places, we have a lot!
    spi is there, but not used yet.
    benchmark shows we can handle 432k bytes/sec! (weird coincidence - 432)
    could double uart baud, do some auto-detection or cycle speeds on errors
2021-02-24 refactor, reformat, get bins
2021-07-28 hardware files for variants, limit max transfer bits
2022-05-20 SPI version, no CRC, times out at 10ms to reset SPI peripheral.
2023-03-22 Note about version branches
2023-07-07 fix byte calc for apa102 data, need start and end frame.
    possible to miss a pixel if an apa102 data frame is the smallest (in bytes)
2023-07-07 updated binaries
2025-07-10 apa102 fast data hack. uses RGB565 and gamma for more FPS while maintaining some dynamic range
